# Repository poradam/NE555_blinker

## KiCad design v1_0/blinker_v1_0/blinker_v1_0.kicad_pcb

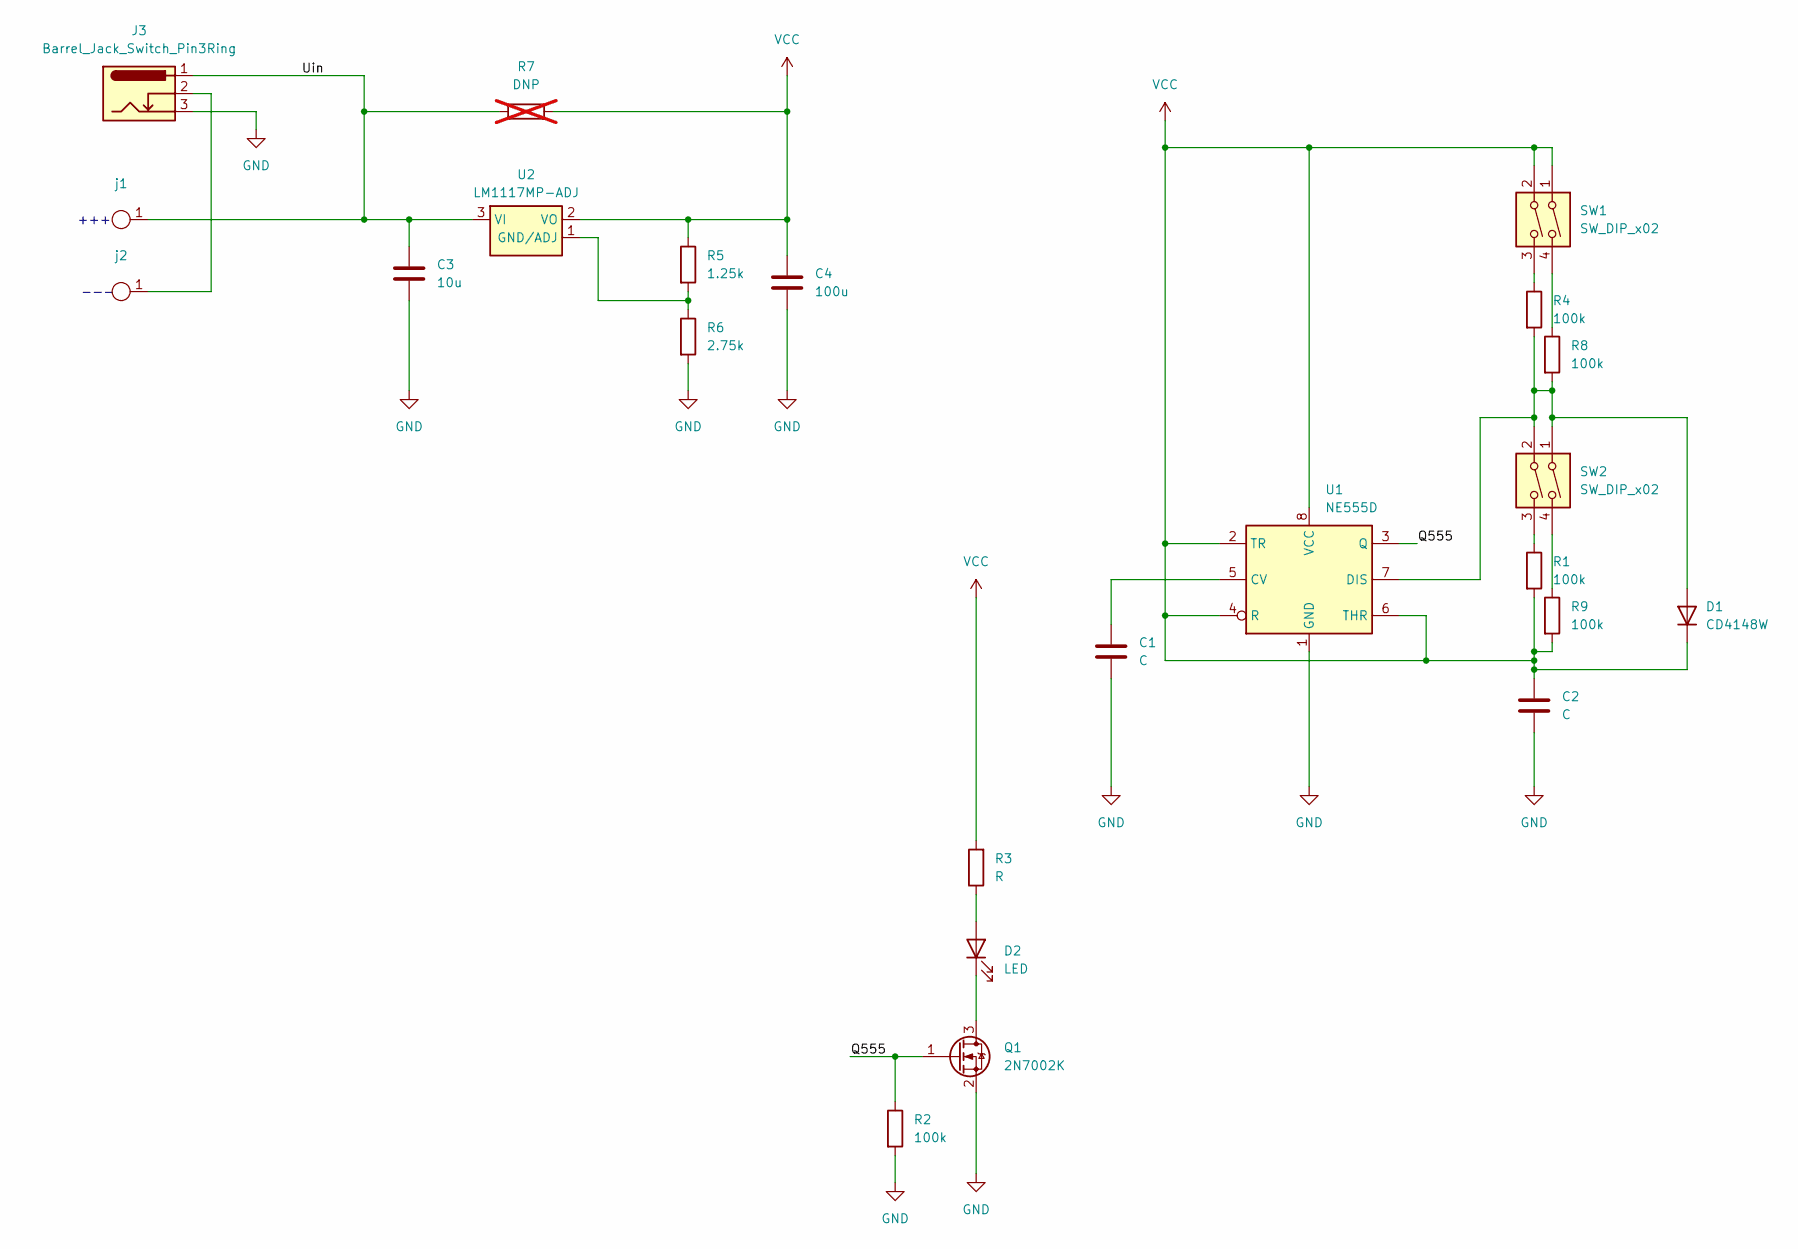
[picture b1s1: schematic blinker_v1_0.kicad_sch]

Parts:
C1, C2: C; C_0603_1608Metric_Pad1.08x0.95mm_HandSolder
C3: 10u; C_0603_1608Metric_Pad1.08x0.95mm_HandSolder
C4: 100u; C_0603_1608Metric_Pad1.08x0.95mm_HandSolder
D1: CD4148W; D_0805_2012Metric
D2: LED; LED_D3.0mm_Horizontal_O1.27mm_Z10.0mm
J3: Barrel_Jack_Switch_Pin3Ring; BarrelJack_GCT_DCJ200-10-A_Horizontal
Q1: 2N7002K; SOT-23
R1, R2, R4, R8, R9: 100k; R_0603_1608Metric
R3: R; R_0603_1608Metric
R5: 1.25k; R_0603_1608Metric
R6: 2.75k; R_0603_1608Metric
R7: DNP; R_0805_2012Metric_Pad1.20x1.40mm_HandSolder; not fitted
SW1, SW2: SW_DIP_x02; DIP-4_W7.62mm
U1: NE555D; SOIC-8_3.9x4.9mm_P1.27mm
U2: LM1117MP-ADJ; SOT-223-3_TabPin2
j1, j2: Pin_D1.0mm_L10.0mm

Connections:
/Q555: Q1.1 (G), R2.1, U1.3 (Q)
/Uin: C3.1, J3.1, R7.1, U2.3 (VI), j1.1
GND: C1.2, C2.2, C3.2, C4.2, J3.3, Q1.2 (S), R2.2, R6.2, U1.1 (GND)
unnamed: D1.2 (A), R4.2, R8.2, SW2.1, SW2.2, U1.7 (DIS)
unnamed: D2.2 (A), R3.1
unnamed: D2.1 (K), Q1.3 (D)
unnamed: J3.2, j2.1
unnamed: R1.1, SW2.3
unnamed: R4.1, SW1.3
unnamed: R8.1, SW1.4
unnamed: R9.1, SW2.4
unnamed: C1.1, U1.5 (CV)
unnamed: R5.2, R6.1, U2.1 (GND/ADJ)
VCC: C2.1, C4.1, D1.1 (K), R1.2, R3.2, R5.1, R7.2, R9.2, SW1.1, SW1.2, U1.2 (TR), U1.4 (R), U1.6 (THR), U1.8 (VCC), U2.2 (VO)

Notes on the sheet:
+++
---

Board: 2 copper layers, 23 parts (0 on the bottom side), 14 nets, no tracks yet.

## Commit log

2024-10-07 second commit
2024-10-08 lyt started
2024-10-09 lyt cont, outline is developing
